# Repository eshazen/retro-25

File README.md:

# retro-25
Retro-tech HP-25 calculator clones using Z80

<table>
  <tr><td>
      <td>
      <td>
</table>

## News!

**2023-01-02**

This is **branch "ScopeClock"**.  Building up another CPU board for used as a general purpose computer for the scope clock, along with the DAC/Interface board from that project, which (whew!) has an actual UART for the serial port.

**2021-01-01**

Time for something new!  The VFD HP-25 is cool and all, but I've lusted after an HP-97 most of my life, plus I love nixie tubes!  Starting to think about a nixie-display HP-97 emulator.  Probably no card reader, but a small printer is certainly doable.  Inspiration from Oliver De Smet (archived elswhere in this repository just in case):

* https://www.hpmuseum.org/cgi-sys/cgiwrap/hpmuseum/archv020.cgi?read=204526
* https://sites.google.com/site/olivier2smet2/hp_projects/hp97

**2020-10-10**

I gave a talk at the HPCC 2020 conference on these calculators.  You can see my slides here:
http://www.hpcc.org/conferences/HPCC2020/HPCC2020_04_Retro_25_revC.pdf

Built a new version with VFD display tubes!

See <a href="https://github.com/eshazen/retro-25/tree/master/notes/VFD-Display">notes</a>.

## What's here

`hardware` has the design files for the CPU and keyboard/display boards

* `firmware/bootloader` has a small serial/flash bootloader which should be programmed at $0000
* `firmware/calc` has the main calculator operating firmware
* `firmware/umon` has a simple Z80 monitor I wrote for debugging
* `firmware/basic` has a hacked version of MS BASIC (4K integer version from 1978)
* `util` has some utility software, including: firmware loader, program loader, stack/register clip utility, simple assembler for HP-25 programs, and some template and example programs

## Hardware
The hardware consists of two boards, a CPU board and an LED+display board.

### CPU board ECOs (mistakes!)

* D2 in the reset circuit - silkscreen is backwards
* U1 pin 11 must be wired to J17 pin 11
* BUSRQ should be tied high or pulled up.  Solder a 1k resistor (or just a wire) from the Z80 (U3) pin 25 to +5V

Also, recommend to cut the trace to nWE on the EEPROM (U4, pin 27) and wire from pin 27 to pin 28.  This disables writing to the EEPROM.  Not essential, but I recommend programming the EEPROM separately in a programmer.  Rogue code can easily wear out the EEPROM (as I found the hard way!) if writing is enabled.  You have been warned.

### Memory and I/O map

The memory map is very simple:

```
EEPROM | 0000-7FFF
RAM    | 8000-FFFF
```
There are six decoded I/O ports:

port | name          | bits  | description
--- | -------------  | ----- | ---------
00 | KB (write only) | bit 0 | KB column 1
"   | "                | bit 1 | KB column 2
"   | "                | bit 2 | KB column 3
"   | "                | bit 3 | KB column 4
"   | "                | bit 4 | KB column 5 and switches
"   | "                | bit 5 | -not used-
"   | "                | bit 6 | LED on CPU board
"   | "                | bit 7 | Serial output
40 | Digits 0-7      | bits 0-7 | ICM7218 display data
41 | Digits 0-7      | bits 0-7 | ICM7218 control data
80 | KB (read only)  | bit 0 | KB row 1
"   | "                | bit 1 | KB row 2
"   | "                | bit 2 | KB row 3
"   | "                | bit 3 | KB row 4
"   | "                | bit 4 | KB row 5
"   | "                | bit 5 | KB row 6
"   | "                | bit 6 | KB row 7
"   | "                | bit 7 | Serial input
c0 | Digits 8-11     | bits 0-7 | ICM7218 display data
c1 | Digits 8-11     | bits 0-7 | ICM7218 control data

All ports except `80` are write-only; port `80` is read-only.

A bit-banged serial port using an FTDI USB adapter is provided
as bit 7 of ports `00` and `80`.  Note that these ports share
keyboard scanning functions, so the code must be carefully written
if both functions are used simultaneously.

There are no interrupts.

## Firmware

See `firmware/calc` for calculator operating program

See `util` for assembler and loader utilities

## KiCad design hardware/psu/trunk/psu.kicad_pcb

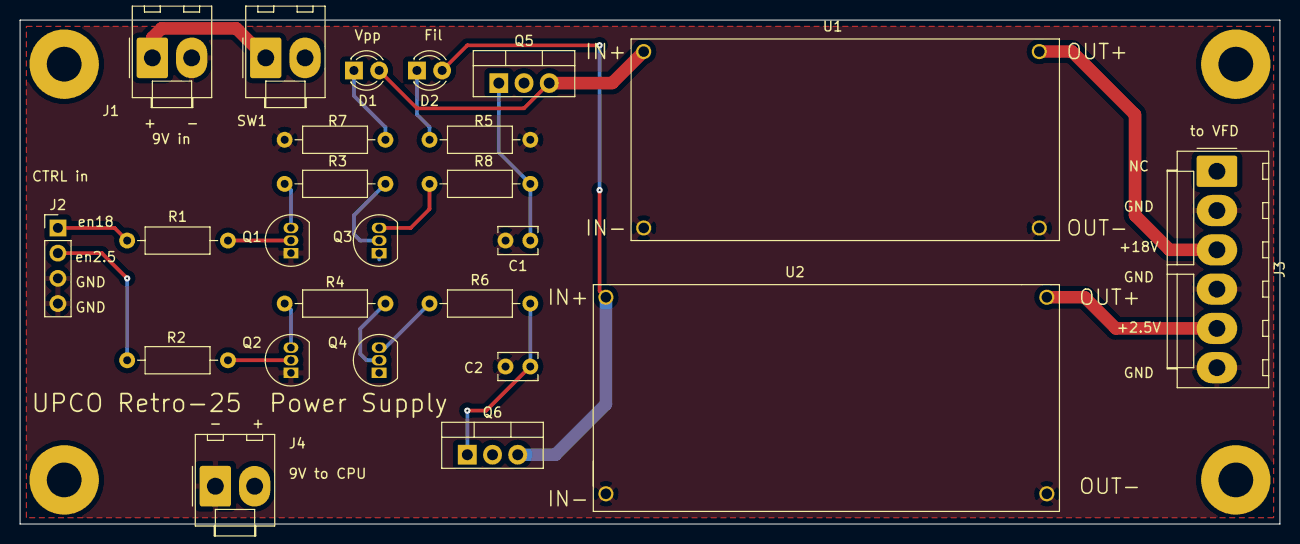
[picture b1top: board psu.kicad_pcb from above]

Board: 2 copper layers, 127.0 x 50.8 mm, 25 parts (0 on the bottom side), 21 nets.

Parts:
C1, C2: 0.1uF; C_Disc_D3.8mm_W2.6mm_P2.50mm
D1, D2: LED; LED_D3.0mm
J1, J4: Conn_01x02_Male; Molex_KK-396_A-41791-0002_1x02_P3.96mm_Vertical
J2: Conn_01x04_Male; PinHeader_1x04_P2.54mm_Vertical
J3: Conn_01x06_Male; Molex_KK-396_A-41791-0006_1x06_P3.96mm_Vertical
Q1, Q2: 2N3904; TO-92_Inline
Q3, Q4: 2N3906; TO-92_Inline
Q5, Q6: IRF540N; TO-220-3_Vertical
R1, R2, R3, R4, R5, R6: R_US; R_Axial_DIN0207_L6.3mm_D2.5mm_P10.16mm_Horizontal
R7: 2.5k; R_Axial_DIN0207_L6.3mm_D2.5mm_P10.16mm_Horizontal
R8: 150; R_Axial_DIN0207_L6.3mm_D2.5mm_P10.16mm_Horizontal
SW1: SW_SPST; Molex_KK-396_A-41791-0002_1x02_P3.96mm_Vertical
U1: BOOST; ebay_XL6009
U2: BUCK; ebay_buck

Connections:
+9V: J4.2, Q3.1, Q4.1, Q5.2, Q6.2, SW1.2
GND: C1.2, C2.2, J1.2, J2.3, J2.4, J3.2, J3.4, J3.6, J4.1, Q1.1, Q2.1, R7.1, R8.1, U1.2, U1.4, U2.2, U2.4
unnamed: C1.1, Q5.1, R5.2
unnamed: C2.1, Q6.1, R6.2
unnamed: D1.1, R7.2
unnamed: D1.2, Q5.3, U1.1
unnamed: D2.1, R8.2
unnamed: D2.2, Q6.3, U2.1
unnamed: J1.1, SW1.1
unnamed: J2.1, R1.2
unnamed: J2.2, R2.2
unnamed: J3.3, U1.3
unnamed: J3.5, U2.3
unnamed: Q1.2, R1.1
unnamed: Q1.3, R3.2
unnamed: Q2.2, R2.1
unnamed: Q2.3, R4.2
unnamed: Q3.2, R3.1
unnamed: Q3.3, R5.1
unnamed: Q4.2, R4.1
unnamed: Q4.3, R6.1

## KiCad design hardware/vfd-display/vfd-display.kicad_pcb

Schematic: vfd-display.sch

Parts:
C1, C2, C5, C7, C9, C11, C12: .01uF; C_Disc_D3.8mm_W2.6mm_P2.50mm
C3, C6: 1uF 50V; C_Disc_D3.8mm_W2.6mm_P2.50mm
C4, C10: 10uF; C_Disc_D3.8mm_W2.6mm_P2.50mm
C8: 10nF 50V; C_Disc_D3.8mm_W2.6mm_P2.50mm
D1, D2: LED; LED_D3.0mm
J1: conn_2x3; PinHeader_2x03_P2.54mm_Vertical
J2: Conn_01x06_Male; Molex_KK-396_A-41791-0006_1x06_P3.96mm_Vertical
J3: Conn_02x08_Odd_Even; PinHeader_2x08_P2.54mm_Vertical
R1: 100; R_Axial_DIN0207_L6.3mm_D2.5mm_P10.16mm_Horizontal
R2: OMIT; R_Axial_DIN0207_L6.3mm_D2.5mm_P10.16mm_Horizontal
R3, R5, R6: 10k; R_Axial_DIN0207_L6.3mm_D2.5mm_P10.16mm_Horizontal
R4, R7: 470; R_Axial_DIN0207_L6.3mm_D2.5mm_P10.16mm_Horizontal
U1, U2, U5, U6, U7, U8, U9, U10, U13, U14, U15, U18: IV-6; iv-6v2
U3, U4, U11, U12, U17: HV5812; DIP-28_W15.24mm_LongPads
U16: LM1084-ADJ; TO-220-3_Vertical
U19: 74LS125; DIP-14_W7.62mm_LongPads
U20: 74LS174; DIP-16_W7.62mm_LongPads

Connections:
+1V2: C10.1, U1.7 (F1), U2.7 (F1), U5.7 (F1), U6.7 (F1), U7.7 (F1), U8.7 (F1), U9.7 (F1), U10.7 (F1), U13.7 (F1), U14.7 (F1), U15.7 (F1), U16.1, U16.2, U18.7 (F1)
+2V5: C4.1, J2.5, U16.3
+5V: C1.1, C2.1, C5.1, C7.1, C9.1, C11.1, C12.1, J2.1, J3.1, J3.3, R3.2, R4.1, R5.2, R6.2, R7.1, U3.28 (VDD), U4.28 (VDD), U11.28 (VDD), U12.28 (VDD), U17.28 (VDD), U19.14, U20.1, U20.16
/A0: J3.15
/BL: U3.13 (BL), U4.13 (BL), U11.13 (BL), U12.13 (BL), U17.13 (BL), U20.10
/CLK: U3.15 (CLK), U4.15 (CLK), U11.15 (CLK), U12.15 (CLK), U17.15 (CLK), U20.7
/D0: J3.2, U19.3, U20.3
/D1: J3.4, U19.6, U20.4
/D2: J3.6, U19.8, U20.6
/D3: J3.8, U19.11, U20.11
/D4: J3.10, U20.13
/D5: J3.12, U20.14
/D6: J3.14
/D7: J3.16
/DIN: U4.27 (DIN), U20.2
/DOUT: U17.2 (DOUT), U19.2
/GRID: C8.1, R1.2, R2.2, U1.9 (G), U2.9 (G), U5.9 (G), U6.9 (G), U7.9 (G), U8.9 (G), U9.9 (G), U10.9 (G), U13.9 (G), U14.9 (G), U15.9 (G), U18.9 (G)
/STB: U3.16 (STB), U4.16 (STB), U11.16 (STB), U12.16 (STB), U17.16 (STB), U20.5
/nLED1: J3.13, U20.9
/nLED2: J3.11, U19.1, U19.4, U19.10, U19.13
GND: C1.2, C2.2, C3.2, C4.2, C5.2, C6.2, C7.2, C8.2, C9.2, C10.2, C11.2, C12.2, J1.2, J1.4, J1.6, J2.2, J2.4, J2.6, J3.5, J3.7, J3.9, R2.1, U1.8 (F2), U2.8 (F2), U3.14 (GND), U4.14 (GND), U5.8 (F2), U6.8 (F2), U7.8 (F2), U8.8 (F2), U9.8 (F2), U10.8 (F2), U11.14 (GND), U12.14 (GND), U13.8 (F2), U14.8 (F2), U15.8 (F2), U17.14 (GND), U18.8 (F2), U19.7, U20.8
unnamed: D1.1, R4.2
unnamed: D1.2, U20.15
unnamed: D2.1, R7.2
unnamed: D2.2, U20.12
unnamed: J1.1, R3.1, U19.5
unnamed: J1.3, R5.1, U19.9
unnamed: J1.5, R6.1, U19.12
unnamed: U1.1 (SegB), U3.26 (OUT1)
unnamed: U1.2 (SegA), U3.25 (OUT2)
unnamed: U1.3 (SegG), U3.24 (OUT3)
unnamed: U1.4 (SegF), U3.23 (OUT4)
unnamed: U1.5 (SegE), U3.22 (OUT5)
unnamed: U1.6 (SegD), U3.21 (OUT6)
unnamed: U1.10 (SegC), U3.20 (OUT7)
unnamed: U1.11 (DP), U3.19 (OUT8)
unnamed: U2.1 (SegB), U4.26 (OUT1)
unnamed: U2.2 (SegA), U4.25 (OUT2)
unnamed: U2.3 (SegG), U4.24 (OUT3)
unnamed: U2.4 (SegF), U4.23 (OUT4)
unnamed: U2.5 (SegE), U4.22 (OUT5)
unnamed: U2.6 (SegD), U4.21 (OUT6)
unnamed: U2.10 (SegC), U4.20 (OUT7)
unnamed: U2.11 (DP), U4.19 (OUT8)
unnamed: U3.3 (OUT20), U7.4 (SegF)
unnamed: U3.4 (OUT19), U7.3 (SegG)
unnamed: U3.5 (OUT18), U7.2 (SegA)
unnamed: U3.6 (OUT17), U7.1 (SegB)
unnamed: U3.7 (OUT16), U5.11 (DP)
unnamed: U3.8 (OUT15), U5.10 (SegC)
unnamed: U3.9 (OUT14), U5.6 (SegD)
unnamed: U3.10 (OUT13), U5.5 (SegE)
unnamed: U3.11 (OUT12), U5.4 (SegF)
unnamed: U3.12 (OUT11), U5.3 (SegG)
unnamed: U3.17 (OUT10), U5.2 (SegA)
unnamed: U3.18 (OUT9), U5.1 (SegB)
unnamed: U4.3 (OUT20), U8.4 (SegF)
unnamed: U4.4 (OUT19), U8.3 (SegG)
unnamed: U4.5 (OUT18), U8.2 (SegA)
unnamed: U4.6 (OUT17), U8.1 (SegB)
unnamed: U4.7 (OUT16), U6.11 (DP)
unnamed: U4.8 (OUT15), U6.10 (SegC)
unnamed: U4.9 (OUT14), U6.6 (SegD)
unnamed: U4.10 (OUT13), U6.5 (SegE)
unnamed: U4.11 (OUT12), U6.4 (SegF)
unnamed: U4.12 (OUT11), U6.3 (SegG)
unnamed: U4.17 (OUT10), U6.2 (SegA)
unnamed: U4.18 (OUT9), U6.1 (SegB)
unnamed: U10.1 (SegB), U12.22 (OUT5)
unnamed: U10.2 (SegA), U12.21 (OUT6)
unnamed: U10.3 (SegG), U12.20 (OUT7)
unnamed: U10.4 (SegF), U12.19 (OUT8)
unnamed: U10.5 (SegE), U12.18 (OUT9)
unnamed: U10.6 (SegD), U12.17 (OUT10)
unnamed: U10.10 (SegC), U12.12 (OUT11)
unnamed: U10.11 (DP), U12.11 (OUT12)
unnamed: U11.2 (DOUT), U17.27 (DIN)
unnamed: U11.3 (OUT20), U13.11 (DP)
unnamed: U11.4 (OUT19), U13.10 (SegC)
unnamed: U11.5 (OUT18), U13.6 (SegD)
unnamed: U11.6 (OUT17), U13.5 (SegE)
unnamed: U11.7 (OUT16), U13.4 (SegF)
unnamed: U11.8 (OUT15), U13.3 (SegG)
unnamed: U11.9 (OUT14), U13.2 (SegA)
unnamed: U11.10 (OUT13), U13.1 (SegB)
unnamed: U9.11 (DP), U11.11 (OUT12)
unnamed: U9.10 (SegC), U11.12 (OUT11)
unnamed: U9.6 (SegD), U11.17 (OUT10)
unnamed: U9.5 (SegE), U11.18 (OUT9)
unnamed: U9.4 (SegF), U11.19 (OUT8)
unnamed: U9.3 (SegG), U11.20 (OUT7)
unnamed: U9.2 (SegA), U11.21 (OUT6)
unnamed: U9.1 (SegB), U11.22 (OUT5)
unnamed: U7.11 (DP), U11.23 (OUT4)
unnamed: U7.10 (SegC), U11.24 (OUT3)
unnamed: U7.6 (SegD), U11.25 (OUT2)
unnamed: U7.5 (SegE), U11.26 (OUT1)
unnamed: U3.2 (DOUT), U11.27 (DIN)
unnamed: U3.27 (DIN), U12.2 (DOUT)
unnamed: U12.3 (OUT20), U14.11 (DP)
unnamed: U12.4 (OUT19), U14.10 (SegC)
unnamed: U12.5 (OUT18), U14.6 (SegD)
unnamed: U12.6 (OUT17), U14.5 (SegE)
unnamed: U12.7 (OUT16), U14.4 (SegF)
unnamed: U12.8 (OUT15), U14.3 (SegG)
unnamed: U12.9 (OUT14), U14.2 (SegA)
unnamed: U12.10 (OUT13), U14.1 (SegB)
unnamed: U8.11 (DP), U12.23 (OUT4)
unnamed: U8.10 (SegC), U12.24 (OUT3)
unnamed: U8.6 (SegD), U12.25 (OUT2)
unnamed: U8.5 (SegE), U12.26 (OUT1)
unnamed: U4.2 (DOUT), U12.27 (DIN)
unnamed: U15.1 (SegB), U17.26 (OUT1)
unnamed: U15.2 (SegA), U17.25 (OUT2)
unnamed: U15.3 (SegG), U17.24 (OUT3)
unnamed: U15.4 (SegF), U17.23 (OUT4)
unnamed: U15.5 (SegE), U17.22 (OUT5)
unnamed: U15.6 (SegD), U17.21 (OUT6)
unnamed: U15.10 (SegC), U17.20 (OUT7)
unnamed: U15.11 (DP), U17.19 (OUT8)
unnamed: U17.7 (OUT16), U18.11 (DP)
unnamed: U17.8 (OUT15), U18.10 (SegC)
unnamed: U17.9 (OUT14), U18.6 (SegD)
unnamed: U17.10 (OUT13), U18.5 (SegE)
unnamed: U17.11 (OUT12), U18.4 (SegF)
unnamed: U17.12 (OUT11), U18.3 (SegG)
unnamed: U17.17 (OUT10), U18.2 (SegA)
unnamed: U17.18 (OUT9), U18.1 (SegB)
VPP: C3.1, C6.1, J2.3, R1.1, U3.1 (VPP), U4.1 (VPP), U11.1 (VPP), U12.1 (VPP), U17.1 (VPP)

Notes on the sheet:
5V power for chips, low current
Filaments
CPU board
Power
Jumpers
Retro-25 Calculator
VFD Display Expansion Board

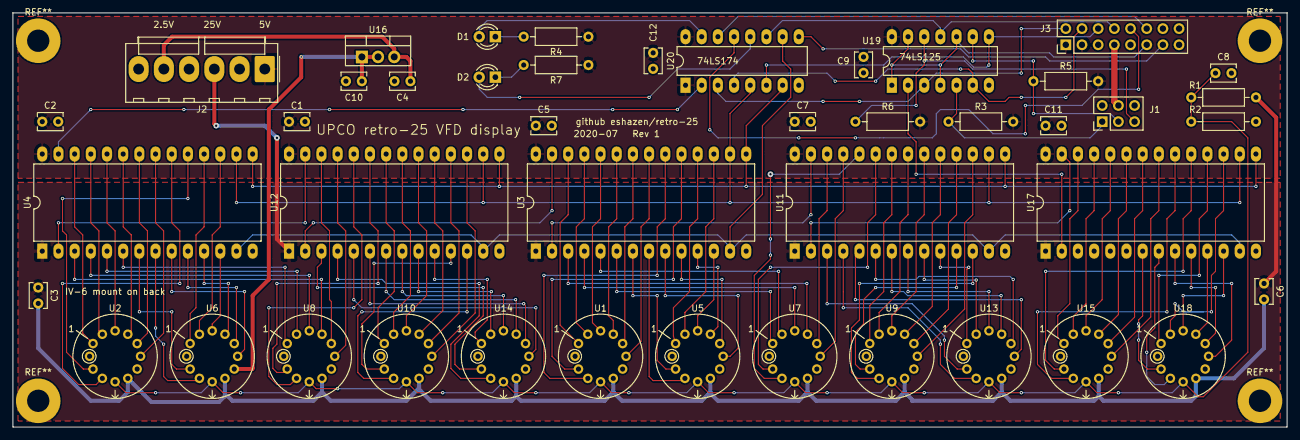
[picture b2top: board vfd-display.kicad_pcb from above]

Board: 2 copper layers, 200.0 x 65.0 mm, 44 parts (0 on the bottom side), 126 nets.

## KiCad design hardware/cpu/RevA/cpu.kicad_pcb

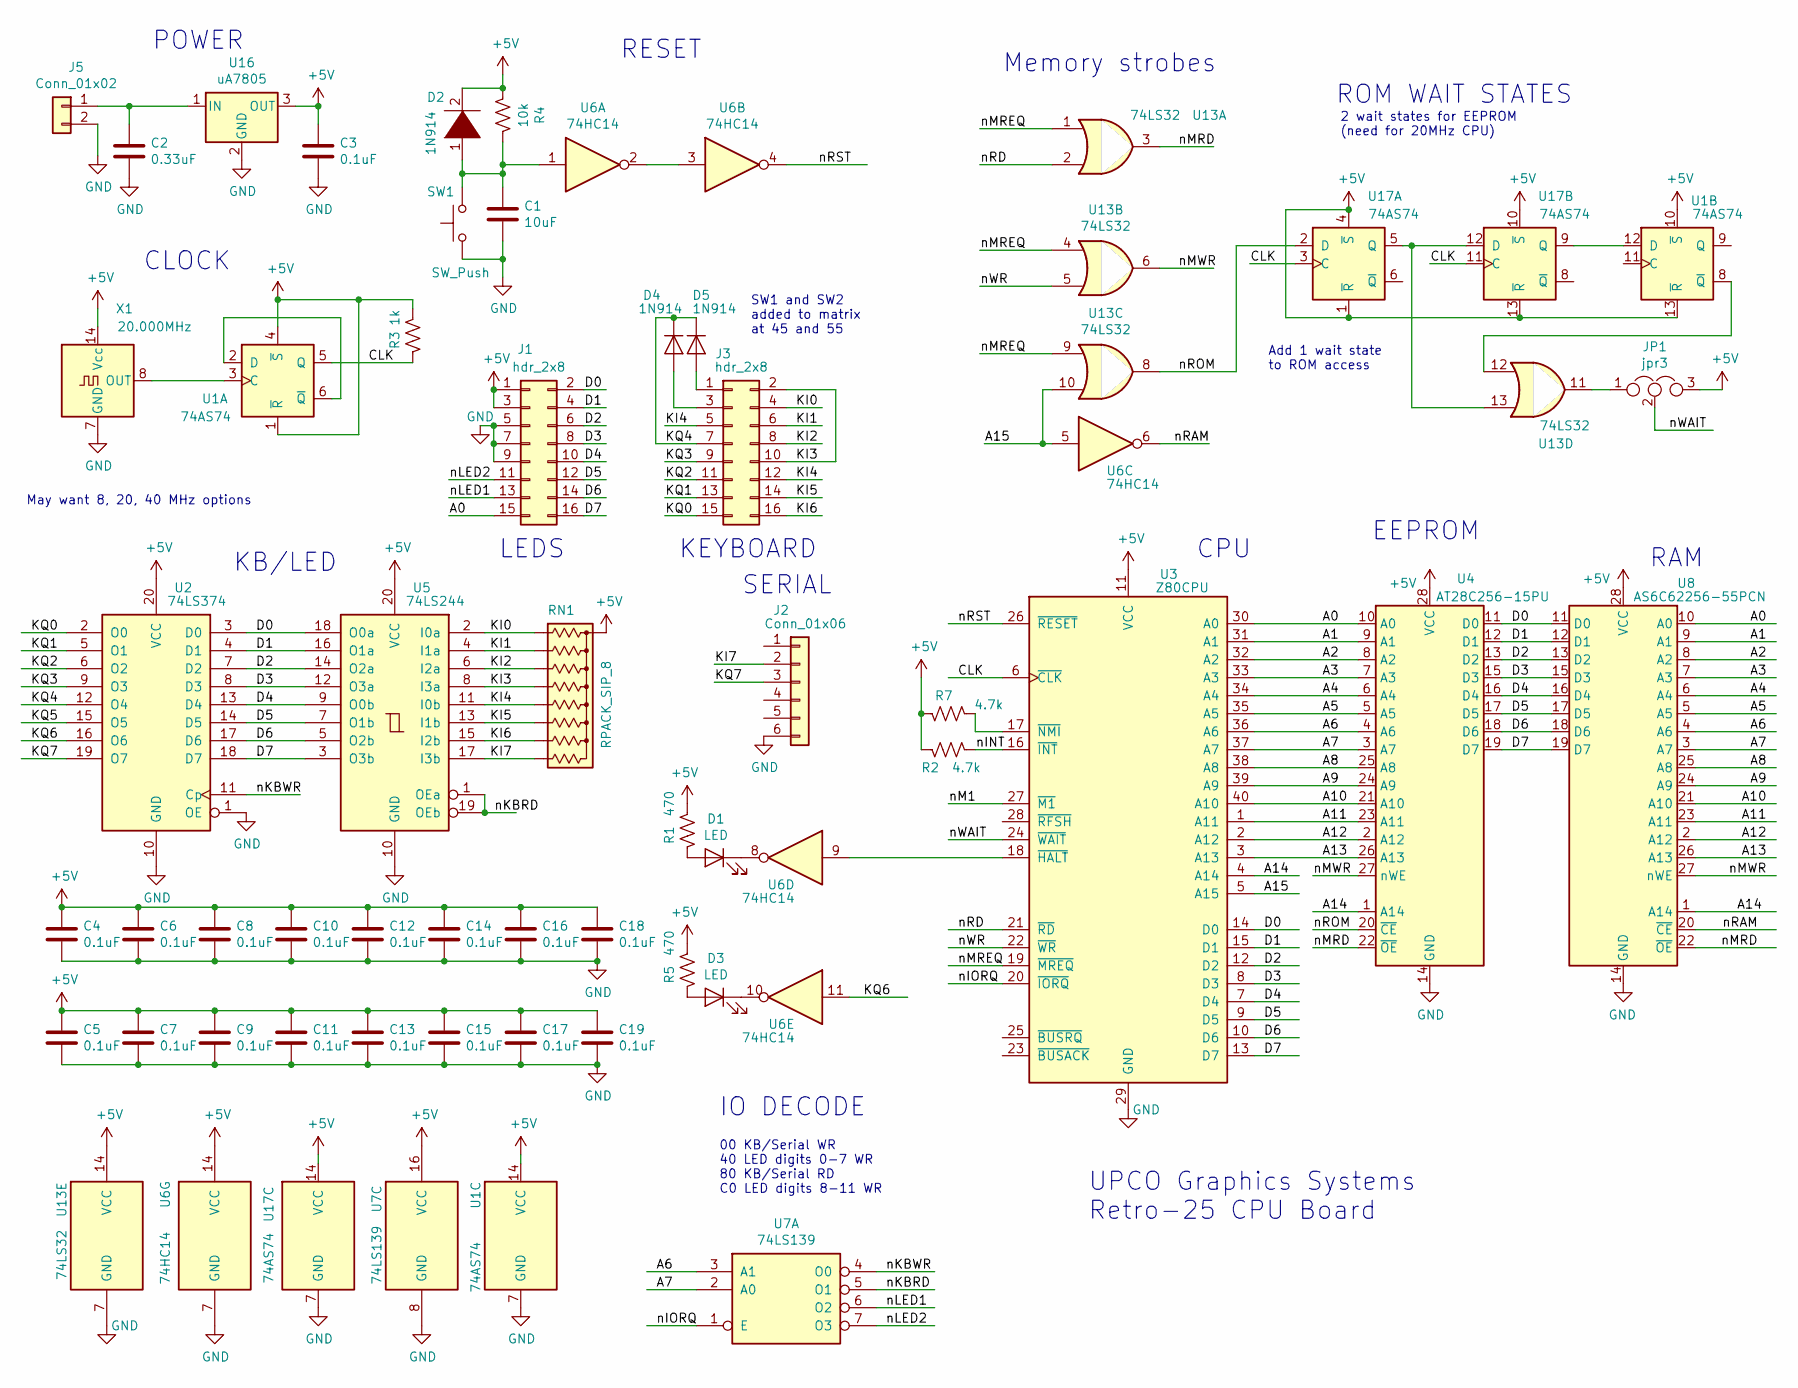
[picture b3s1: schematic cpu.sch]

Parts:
C1: 10uF
C2: 0.33uF
C3, C4, C5, C6, C7, C8, C9, C10, C11, C12, C13, C14, C15, C16, C17, C18, C19: 0.1uF
D1, D3: LED
D2: 1N914
D4, D5: 1N914; D_DO-35_SOD27_P7.62mm_Horizontal
J1, J3: hdr_2x8
J2: Conn_01x06
J5: Conn_01x02
JP1: jpr3
R1, R5: 470
R2, R7: 4.7k
R3: 1k
R4: 10k
RN1: RPACK_SIP_8; R_Array_SIP9
SW1: SW_Push
U1, U17: 74AS74
U2: 74LS374
U3: Z80CPU
U4: AT28C256-15PU; DIP-28_W15.24mm
U5: 74LS244
U6: 74HC14
U7: 74LS139
U8: AS6C62256-55PCN; DIP-28_W15.24mm
U13: 74LS32
U16: uA7805
X1: 20.000MHz; Oscillator_DIP-14

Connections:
+5V: C3.1, C4.1, C5.1, C6.1, C7.1, C8.1, C9.1, C10.1, C11.1, C12.1, C13.1, C14.1, C15.1, C16.1, C17.1, C18.1, C19.1, D2.2 (A), J1.1, J1.3, JP1.3, R1.2, R2.2, R3.2, R4.2, R5.2, R7.2, RN1.1 (common), U1.1 (~R), U1.4 (~S), U1.10 (~S), U1.13 (~R), U1.14 (VCC), U2.20 (VCC), U3.11 (VCC), U4.28 (VCC), U5.20 (VCC), U6.14 (VCC), U7.16 (VCC), U8.28 (VCC), U13.14 (VCC), U16.3 (OUT), U17.1 (~R), U17.4 (~S), U17.10 (~S), U17.13 (~R), U17.14 (VCC), X1.14 (Vcc)
/A0: J1.15, U3.30 (A0), U4.10 (A0), U8.10 (A0)
/A1: U3.31 (A1), U4.9 (A1), U8.9 (A1)
/A2: U3.32 (A2), U4.8 (A2), U8.8 (A2)
/A3: U3.33 (A3), U4.7 (A3), U8.7 (A3)
/A4: U3.34 (A4), U4.6 (A4), U8.6 (A4)
/A5: U3.35 (A5), U4.5 (A5), U8.5 (A5)
/A6: U3.36 (A6), U4.4 (A6), U7.3 (A1), U8.4 (A6)
/A7: U3.37 (A7), U4.3 (A7), U7.2 (A0), U8.3 (A7)
/A8: U3.38 (A8), U4.25 (A8), U8.25 (A8)
/A9: U3.39 (A9), U4.24 (A9), U8.24 (A9)
/A10: U3.40 (A10), U4.21 (A10), U8.21 (A10)
/A11: U3.1 (A11), U4.23 (A11), U8.23 (A11)
/A12: U3.2 (A12), U4.2 (A12), U8.2 (A12)
/A13: U3.3 (A13), U4.26 (A13), U8.26 (A13)
/A14: U3.4 (A14), U4.1 (A14), U8.1 (A14)
/A15: U3.5 (A15), U6.5, U13.10
/CLK: R3.1, U1.5 (Q), U3.6 (~CLK~), U17.3 (C), U17.11 (C)
/D0: J1.2, U2.3 (D0), U3.14 (D0), U4.11 (D0), U5.18 (O0a), U8.11 (D0)
/D1: J1.4, U2.4 (D1), U3.15 (D1), U4.12 (D1), U5.16 (O1a), U8.12 (D1)
/D2: J1.6, U2.7 (D2), U3.12 (D2), U4.13 (D2), U5.14 (O2a), U8.13 (D2)
/D3: J1.8, U2.8 (D3), U3.8 (D3), U4.15 (D3), U5.12 (O3a), U8.15 (D3)
/D4: J1.10, U2.13 (D4), U3.7 (D4), U4.16 (D4), U5.9 (O0b), U8.16 (D4)
/D5: J1.12, U2.14 (D5), U3.9 (D5), U4.17 (D5), U5.7 (O1b), U8.17 (D5)
/D6: J1.14, U2.17 (D6), U3.10 (D6), U4.18 (D6), U5.5 (O2b), U8.18 (D6)
/D7: J1.16, U2.18 (D7), U3.13 (D7), U4.19 (D7), U5.3 (O3b), U8.19 (D7)
/KI0: J3.4, RN1.2 (R1), U5.2 (I0a)
/KI1: J3.6, RN1.3 (R2), U5.4 (I1a)
/KI2: J3.8, RN1.4 (R3), U5.6 (I2a)
/KI3: J3.2, J3.10, RN1.5 (R4), U5.8 (I3a)
/KI4: J3.5, J3.12, RN1.6 (R5), U5.11 (I0b)
/KI5: J3.14, RN1.7 (R6), U5.13 (I1b)
/KI6: J3.16, RN1.8 (R7), U5.15 (I2b)
/KI7: J2.2, RN1.9 (R8), U5.17 (I3b)
/KQ0: J3.15, U2.2 (O0)
/KQ1: J3.13, U2.5 (O1)
/KQ2: J3.11, U2.6 (O2)
/KQ3: J3.9, U2.9 (O3)
/KQ4: D4.1 (K), D5.1 (K), J3.7, U2.12 (O4)
/KQ5: U2.15 (O5)
/KQ6: U2.16 (O6), U6.11
/KQ7: J2.3, U2.19 (O7)
/nINT: R2.1, U3.16 (~INT~)
/nIORQ: U3.20 (~IORQ~), U7.1 (E)
/nKBRD: U5.1 (OEa), U5.19 (OEb), U7.5 (O1)
/nKBWR: U2.11 (Cp), U7.4 (O0)
/nLED1: J1.13, U7.6 (O2)
/nLED2: J1.11, U7.7 (O3)
/nM1: U3.27 (~M1~)
/nMRD: U4.22 (~OE), U8.22 (~OE), U13.3
/nMREQ: U3.19 (~MREQ~), U13.1, U13.4, U13.9
/nMWR: U4.27 (nWE), U8.27 (nWE), U13.6
/nRAM: U6.6, U8.20 (~CE)
/nRD: U3.21 (~RD~), U13.2
/nROM: U4.20 (~CE), U13.8, U17.2 (D)
/nRST: U3.26 (~RESET~), U6.4
/nWAIT: JP1.2, U3.24 (~WAIT~)
/nWR: U3.22 (~WR~), U13.5
GND: C1.2, C2.2, C3.2, C4.2, C5.2, C6.2, C7.2, C8.2, C9.2, C10.2, C11.2, C12.2, C13.2, C14.2, C15.2, C16.2, C17.2, C18.2, C19.2, J1.5, J1.7, J1.9, J2.6, J5.2, SW1.2, U1.7 (GND), U2.1 (OE), U2.10 (GND), U3.29 (GND), U4.14 (GND), U5.10 (GND), U6.7 (GND), U7.8 (GND), U8.14 (GND), U13.7 (GND), U16.2 (GND), U17.7 (GND), X1.7 (GND)
unnamed: C1.1, D2.1 (K), R4.1, SW1.1, U6.1
unnamed: C2.1, J5.1, U16.1 (IN)
unnamed: D1.1 (K), U6.8
unnamed: D1.2 (A), R1.1
unnamed: D3.1 (K), U6.10
unnamed: D3.2 (A), R5.1
unnamed: D4.2 (A), J3.3
unnamed: D5.2 (A), J3.1
unnamed: JP1.1, U13.11
unnamed: R7.1, U3.17 (~NMI~)
unnamed: U1.2 (D), U1.6 (~Q)
unnamed: U1.3 (C), X1.8 (OUT)
unnamed: U1.8 (~Q), U13.12
unnamed: U1.12 (D), U17.9 (Q)
unnamed: U3.18 (~HALT~), U6.9
unnamed: U6.2, U6.3
unnamed: U13.13, U17.5 (Q), U17.12 (D)

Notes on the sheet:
KB/LED
CLOCK
RESET
CPU
EEPROM
RAM
Memory strobes
ROM WAIT STATES
Add 1 wait state to ROM access
IO DECODE
00 KB/Serial WR 40 LED digits 0-7 WR 80 KB/Serial RD C0 LED digits 8-11 WR
SW1 and SW2 added to matrix at 45 and 55
LEDS
KEYBOARD
SERIAL
POWER
UPCO Graphics Systems Retro-25 CPU Board
2 wait states for EEPROM (need for 20MHz CPU)
May want 8, 20, 40 MHz options

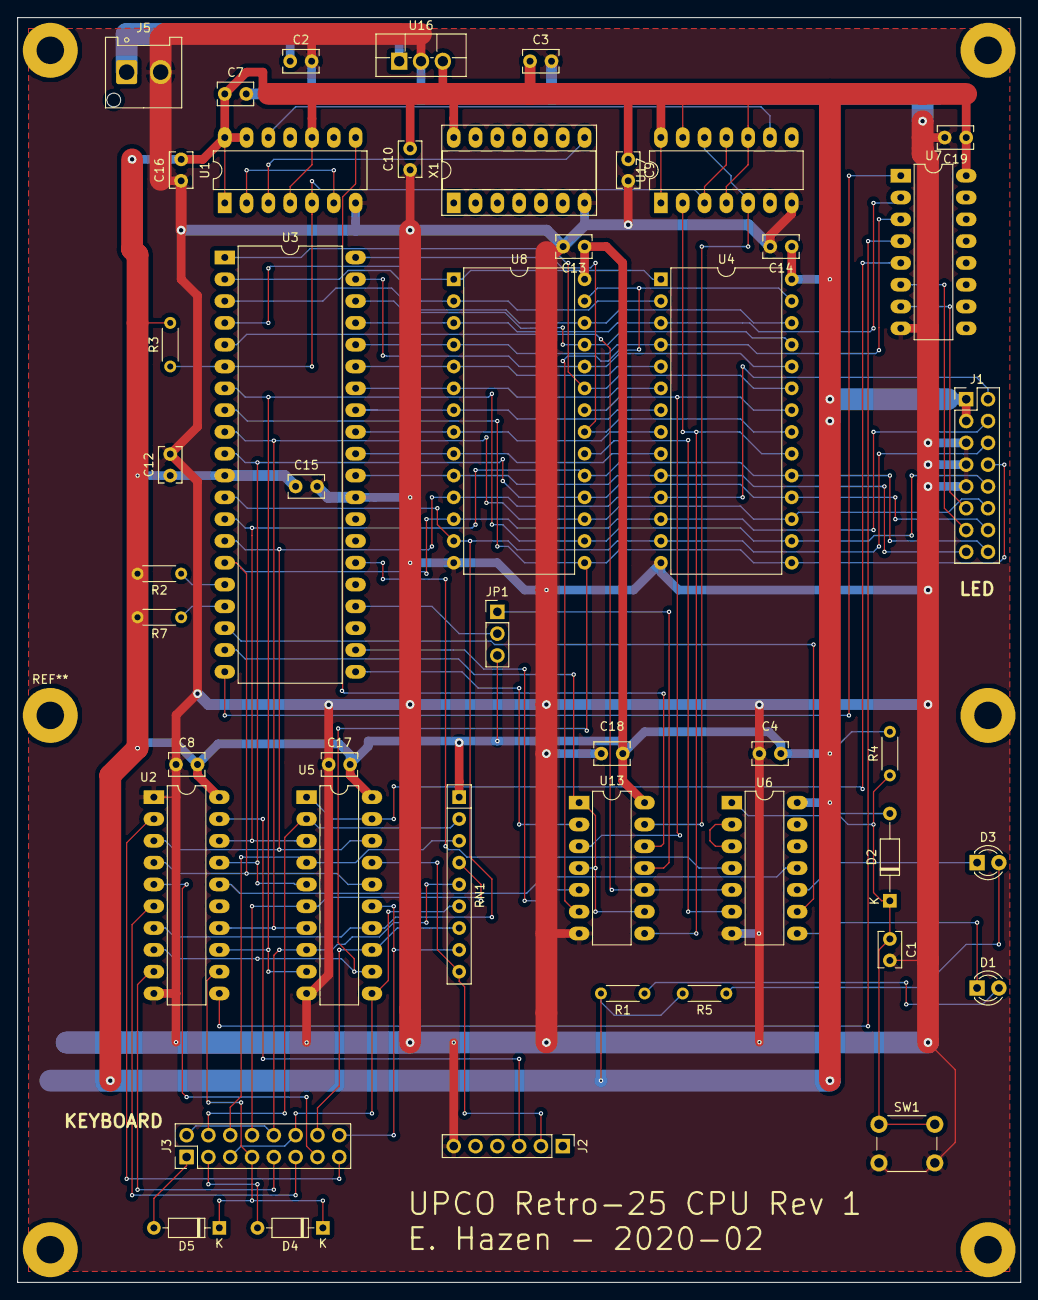
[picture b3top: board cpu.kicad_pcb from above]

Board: 2 copper layers, 116.8 x 147.3 mm, 46 parts (0 on the bottom side), 74 nets.

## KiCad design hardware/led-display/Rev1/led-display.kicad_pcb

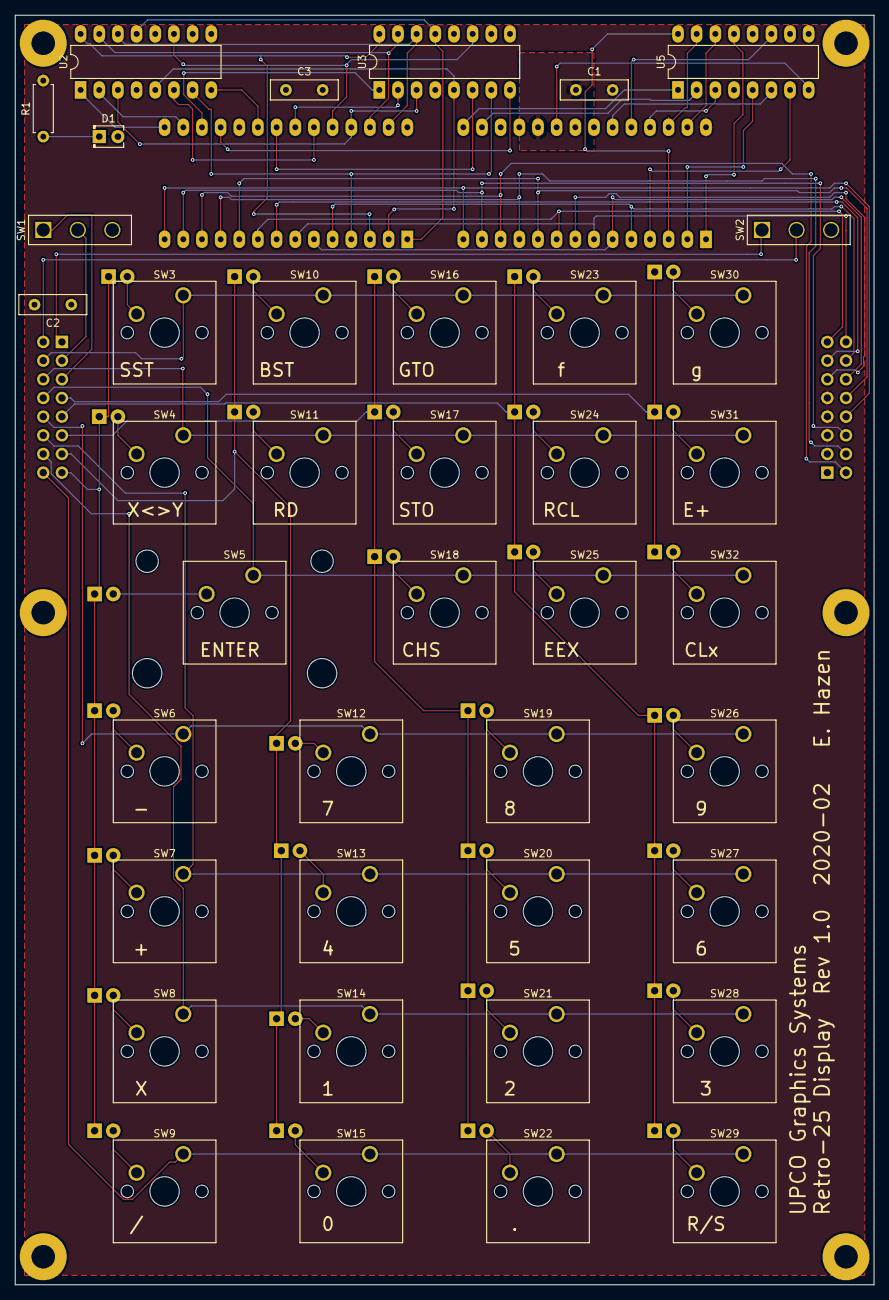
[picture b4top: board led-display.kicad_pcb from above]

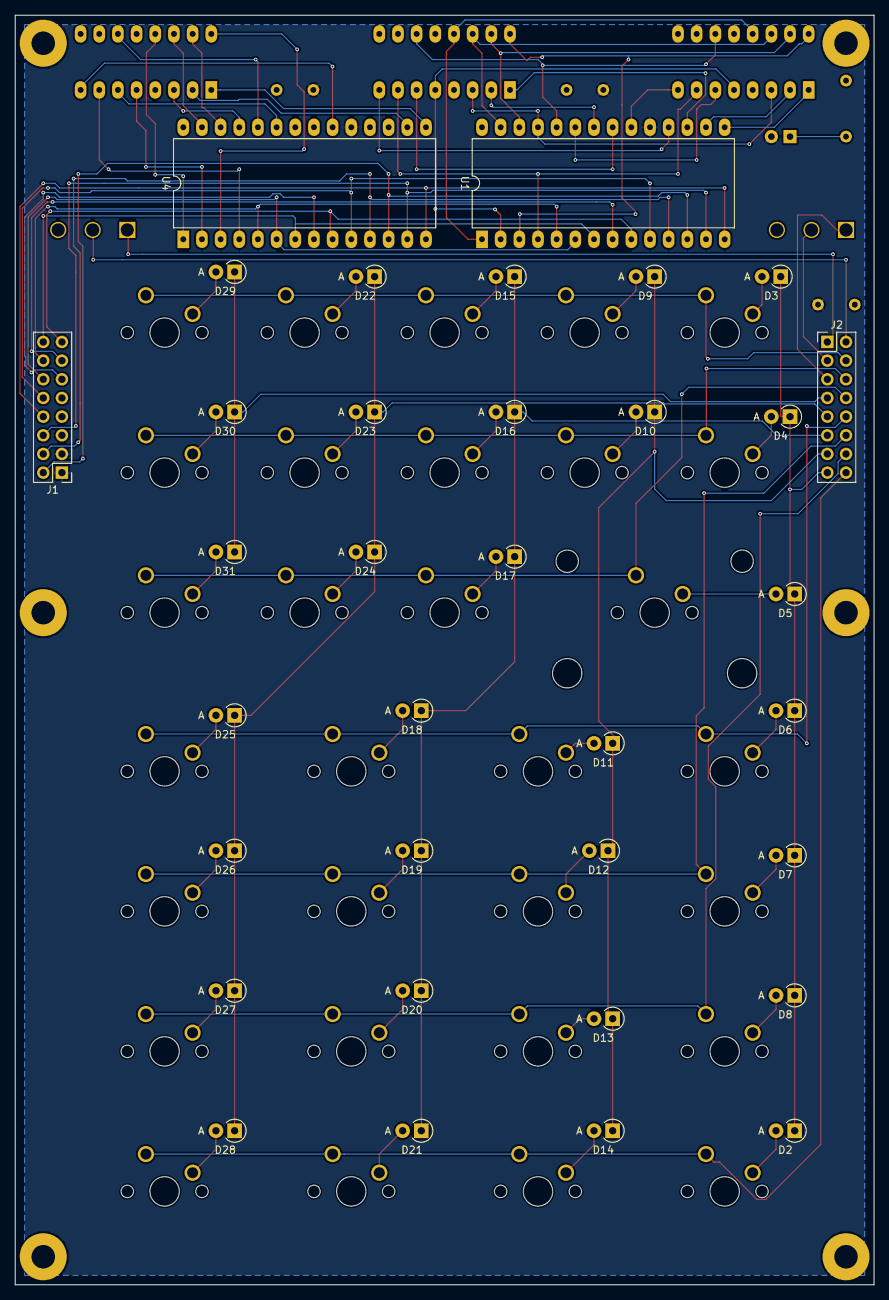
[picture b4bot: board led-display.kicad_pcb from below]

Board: 2 copper layers, 116.8 x 172.7 mm, 74 parts (34 on the bottom side), 88 nets.

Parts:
C1, C2, C3: 0.1uF; C_Disc_D9.0mm_W2.5mm_P5.00mm
D1: LED; LED_D2.0mm_W4.0mm_H2.8mm_FlatTop
D2, D3, D4, D5, D6, D7, D8, D9, D10, D11, D12, D13, D14, D15, D16, D17, D18, D19, D20, D21, D22, D23, D24, D25, D26, D27, D28, D29, D30, D31: 1N914; D_T-1_P2.54mm_Vertical_AnodeUp
J1, J2: C2x8100; PinHeader_2x08_P2.54mm_Vertical
R1: 470; R_Axial_DIN0207_L6.3mm_D2.5mm_P7.62mm_Horizontal
SW1, SW2: SW_SPST; sw_slide_4.7mm
SW3, SW4, SW6, SW7, SW8, SW9, SW10, SW11, SW12, SW13, SW14, SW15, SW16, SW17, SW18, SW19, SW20, SW21, SW22, SW23, SW24, SW25, SW26, SW27, SW28, SW29, SW30, SW31, SW32: MX1A-C1NW; SW_Cherry_MX1A_1.00u_PCB
SW5: MX1A-C1NW; SW_Cherry_MX1A_2.00u_PCB
U1, U4: ICM7218A; DIP-28_W15.24mm_LongPads
U2, U3, U5: LTC-4627JR; DIP-16_W7.62mm_LongPads

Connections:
/D0: J1.2, U1.12, U4.12
/D1: J1.4, U1.11, U4.11
/D2: J1.6, U1.13, U4.13
/D3: J1.8, U1.14, U4.14
/D4: J1.10, U1.10, U4.10
/D5: J1.12, U1.6, U4.6
/D6: J1.14, U1.5, U4.5
/D7: J1.16, U1.7, U4.7
/MODE: J1.15, U1.9, U4.9
/WR2: J1.11, U4.8
GND: C1.2, C2.2, C3.2, J1.5, J1.7, J1.9, R1.2, U1.28, U4.28
unnamed: D1.1, R1.1
unnamed: D2.1, D3.1, D4.1, D5.1, D6.1, D7.1, D8.1, J2.15
unnamed: D2.2, SW9.2
unnamed: D3.2, SW3.2
unnamed: D4.2, SW4.2
unnamed: D5.2, SW5.2
unnamed: D6.2, SW6.2
unnamed: D7.2, SW7.2
unnamed: D8.2, SW8.2
unnamed: D9.2, SW10.2
unnamed: D9.1, D10.1, D11.1, D12.1, D13.1, D14.1, J2.13
unnamed: D10.2, SW11.2
unnamed: D11.2, SW12.2
unnamed: D12.2, SW13.2
unnamed: D13.2, SW14.2
unnamed: D14.2, SW15.2
unnamed: D15.1, D16.1, D17.1, D18.1, D19.1, D20.1, D21.1, J2.11
unnamed: D15.2, SW16.2
unnamed: D16.2, SW17.2
unnamed: D17.2, SW18.2
unnamed: D18.2, SW19.2
unnamed: D19.2, SW20.2
unnamed: D20.2, SW21.2
unnamed: D21.2, SW22.2
unnamed: D22.1, D23.1, D24.1, D25.1, D26.1, D27.1, D28.1, J2.9
unnamed: D22.2, SW23.2
unnamed: D23.2, SW24.2
unnamed: D24.2, SW25.2
unnamed: D25.2, SW26.2
unnamed: D26.2, SW27.2
unnamed: D27.2, SW28.2
unnamed: D28.2, SW29.2
unnamed: D29.1, D30.1, D31.1, J2.7
unnamed: D29.2, SW30.2
unnamed: D30.2, SW31.2
unnamed: D31.2, SW32.2
unnamed: J1.13, U1.8
unnamed: J2.1, SW2.1
unnamed: J2.2, SW2.2
unnamed: J2.3, SW1.2
unnamed: J2.4, SW3.1, SW10.1, SW16.1, SW23.1, SW30.1
unnamed: J2.5, SW1.1
unnamed: J2.6, SW4.1, SW11.1, SW17.1, SW24.1, SW31.1
unnamed: J2.8, SW5.1, SW18.1, SW25.1, SW32.1
unnamed: J2.10, SW6.1, SW12.1, SW19.1, SW26.1
unnamed: J2.12, SW7.1, SW13.1, SW20.1, SW27.1
unnamed: J2.14, SW8.1, SW14.1, SW21.1, SW28.1
unnamed: J2.16, SW9.1, SW15.1, SW22.1, SW29.1
unnamed: U1.1, U2.13, U3.13
unnamed: U1.2, U2.5, U3.5
unnamed: U1.3, U2.16, U3.16
unnamed: U1.4, U2.7, U3.7
unnamed: U1.15, U2.1
unnamed: U1.16, U2.2
unnamed: U1.17, U3.1
unnamed: U1.18, U3.8
unnamed: U1.20, U2.8
unnamed: U1.21, U3.6
unnamed: U1.22, U3.2
unnamed: U1.23, U2.6
unnamed: U1.24, U2.11, U3.11
unnamed: U1.25, U2.3, U3.3
unnamed: U1.26, U2.15, U3.15
unnamed: U1.27, U2.14, U3.14
unnamed: U4.1, U5.13
unnamed: U4.2, U5.5
unnamed: U4.3, U5.16
unnamed: U4.4, U5.7
unnamed: U4.15, U5.1
unnamed: U4.16, U5.2
unnamed: U4.20, U5.8
unnamed: U4.23, U5.6
unnamed: U4.24, U5.11
unnamed: U4.25, U5.3
unnamed: U4.26, U5.15
unnamed: U4.27, U5.14
VCC: C1.1, C2.1, C3.1, D1.2, J1.1, J1.3, U1.19, U4.19

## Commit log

2020-05-09 Upload Rev A/1 Hardware Files
2020-05-09 Editing readme
2020-05-09 Add first version calculator firmware
2020-05-23 Cleaned up the code for an initial commit. Produces a working hex file.
2020-05-23 Add bootloader and update READMEs
2020-05-23 Add eeprom.hex (unverified)
2020-05-23 Add photos
2020-05-24 Tweak readme
2020-05-26 Add features to exit the calc when break received over the serial port and jump to UMON loaded at 0x8100 with a small struct giving the location of the register stack and RAM for debugging.
    Add a file describing internal storage layout and a complete
    matrix of hex codes for stored program steps.
2020-05-26 Update a bit the internal storage note
2020-05-26 Some initial decoding tools
2020-05-27 add assembler, loader
2020-05-27 Update readme, rename firmware loader
2020-05-27 Finish up serial server
2020-05-27 working on readmes
2020-05-27 readme
2020-05-27 Add umon monitor
2020-06-02 various small updates
2020-06-04 Add NASCOM basic modified to run on retro-25
2020-06-18 add more photos
2020-07-01 starting a folder for VFD display version
2020-07-01 vfd photo
2020-07-01 More VFD ideas and drawing
2020-07-01 update drawings
2020-07-01 add some drawing notes
2020-07-01 add some more drawing notes
2020-07-01 Initial schem for VFD display
2020-07-01 Preliminary VFD schematic
2020-07-02 Schematic, footprints, partial placement
2020-07-02 tweak placement
2020-07-03 Rev 1 design for fab
2020-07-03 rev 1 gerber zip
2020-07-03 add 3D model for tubes
2020-07-09 add BOMs
2020-07-10 VFD board photo
2020-07-29 Update schematic PDF
2020-08-02 add display photo
2020-08-02 photos
2020-08-03 First draft VFD support
2020-08-03 VFD display now assembles...
2020-08-03 Add 'V' command to umon for VFD test
2020-08-04 Initial VFD display support
2020-08-06 mech dwgs
2020-08-07 DXF for case
2020-08-13 Update Makefile for VFD/LED targets
2020-08-13 key labels
2020-08-14 fix display blanking
2020-08-14 adding gitignores
2020-08-14 cleaning up
2020-08-14 add PSU
2020-08-14 ordered PCBs
2020-08-29 resistor values
2020-08-29 Power supply control
2020-08-29 tweak photos
2020-08-31 fix bugs in bootloader, make umon base control by makefile
2020-09-01 start HCC talk
2020-09-01 working on slides
2020-10-04 working on talk
2020-10-06 working
2020-10-06 getting there
2020-10-08 Final? talk draft
2020-10-10 Final talk draft
2020-10-12 really final talk
2020-10-27 add current hex files
2021-01-05 Add Olivier De Smet archives
2021-02-05 add linear regression program, add R/S to assembler
2021-02-05 Add 4 flavors of fit
2021-02-05 remove assembler output on make clean
2025-02-19 tweak the keyboard plate
